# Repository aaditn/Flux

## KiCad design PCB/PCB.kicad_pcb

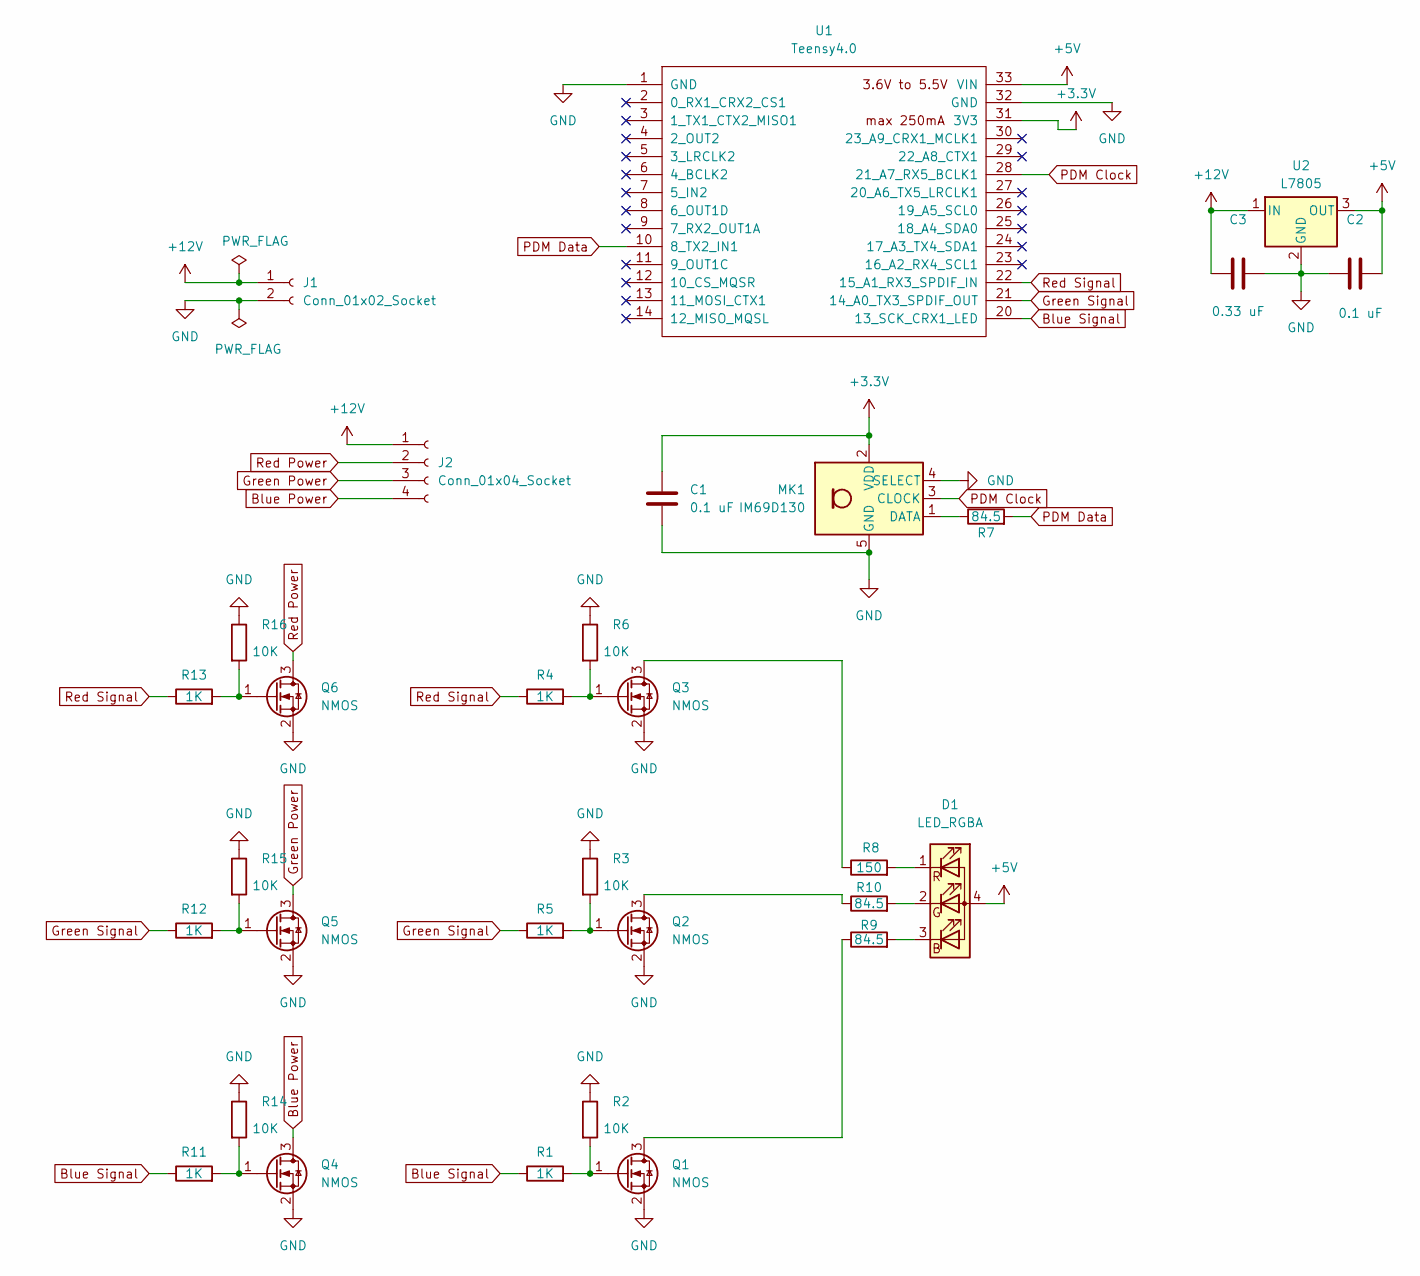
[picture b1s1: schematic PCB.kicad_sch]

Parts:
C1, C2: 0.1 uF; C_0603_1608Metric
C3: 0.33 uF; C_0603_1608Metric
D1: LED_RGBA; 150066M153000
J1: Conn_01x02_Socket; 2.1x5.5_Barrel_Jack
J2: Conn_01x04_Socket; TerminalBlock_Phoenix_MKDS-1,5-4_1x04_P5.00mm_Horizontal
MK1: IM69D130; Infineon_PG-LLGA-5-1
Q1, Q2, Q3, Q4, Q5, Q6: NMOS; SC-59
R1, R4, R5, R11, R12, R13: 1K; R_0603_1608Metric
R2, R3, R6, R14, R15, R16: 10K; R_0603_1608Metric
R7, R9, R10: 84.5; R_0603_1608Metric
R8: 150; R_0603_1608Metric
U1: Teensy4.0; Teensy40
U2: L7805; TO-252-2

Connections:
+3.3V: C1.1, MK1.2 (VDD), U1.31 (3V3)
+5V: C2.2, D1.4 (A), U1.33 (VIN), U2.3 (OUT)
+12V: C3.1, J1.1, J2.1, U2.1 (IN)
Blue Power: J2.4, Q4.3 (D)
Blue Signal: R1.1, R11.1, U1.20 (13_SCK_CRX1_LED)
GND: C1.2, C2.1, C3.2, J1.2, MK1.4 (SELECT), MK1.5 (GND), Q1.2 (S), Q2.2 (S), Q3.2 (S), Q4.2 (S), Q5.2 (S), Q6.2 (S), R2.1, R3.1, R6.1, R14.1, R15.1, R16.1, U1.1 (GND), U1.32 (GND), U2.2 (GND)
Green Power: J2.3, Q5.3 (D)
Green Signal: R5.1, R12.1, U1.21 (14_A0_TX3_SPDIF_OUT)
unnamed: D1.3 (BK), R9.2
unnamed: D1.2 (GK), R10.2
unnamed: D1.1 (RK), R8.2
unnamed: MK1.1 (DATA), R7.1
unnamed: Q1.3 (D), R9.1
unnamed: Q1.1 (G), R1.2, R2.2
unnamed: Q2.3 (D), R10.1
unnamed: Q2.1 (G), R3.2, R5.2
unnamed: Q3.3 (D), R8.1
unnamed: Q3.1 (G), R4.2, R6.2
unnamed: Q4.1 (G), R11.2, R14.2
unnamed: Q5.1 (G), R12.2, R15.2
unnamed: Q6.1 (G), R13.2, R16.2
PDM Clock: MK1.3 (CLOCK), U1.28 (21_A7_RX5_BCLK1)
PDM Data: R7.2, U1.10 (8_TX2_IN1)
Red Power: J2.2, Q6.3 (D)
Red Signal: R4.1, R13.1, U1.22 (15_A1_RX3_SPDIF_IN)

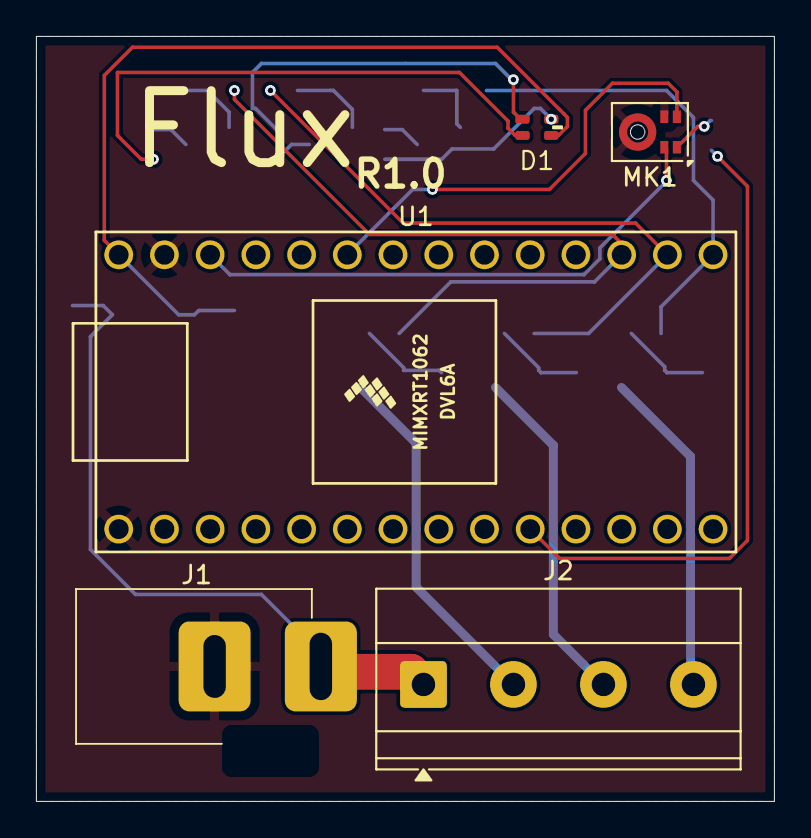
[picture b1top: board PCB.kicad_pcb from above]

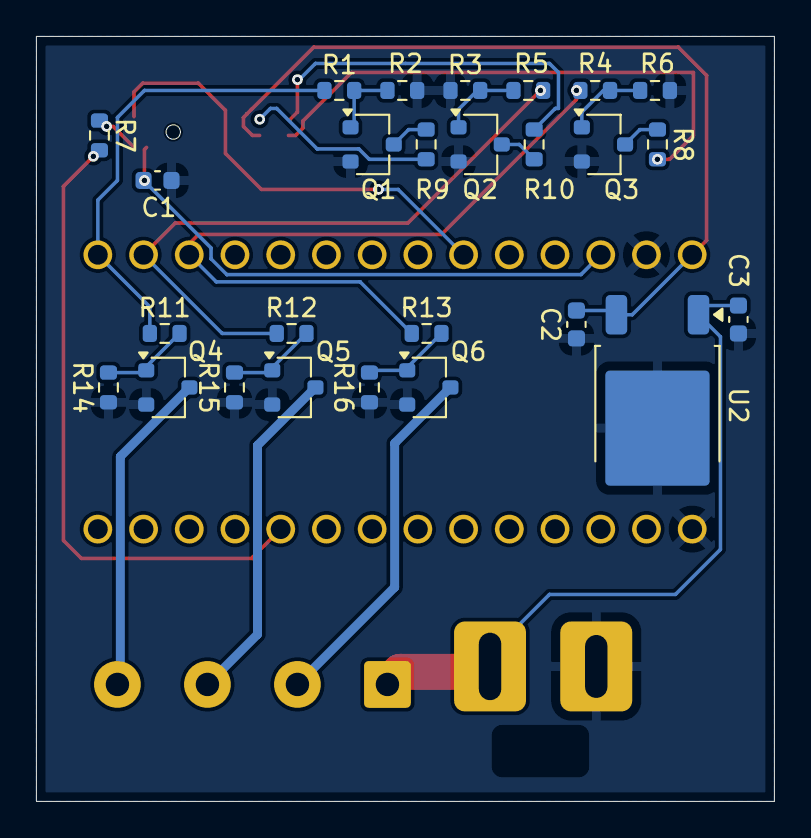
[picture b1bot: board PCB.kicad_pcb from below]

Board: 2 copper layers, 41.0 x 42.5 mm, 31 parts (26 on the bottom side), 25 nets.

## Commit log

2026-01-02 setup
2026-01-02 symbols/footprints take 2
2026-01-03 awaiting led footprint
2026-01-03 schematic complete
2026-01-03 everything done except stupid 1 issue
2026-01-03 Stupid dumb fix
    Also did geographical reannotation
2026-01-04 discussed changes
2026-01-04 BOM Update
